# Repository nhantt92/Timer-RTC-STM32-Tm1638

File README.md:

# Timer-control-boar-hw

- Timer-control-board-hw

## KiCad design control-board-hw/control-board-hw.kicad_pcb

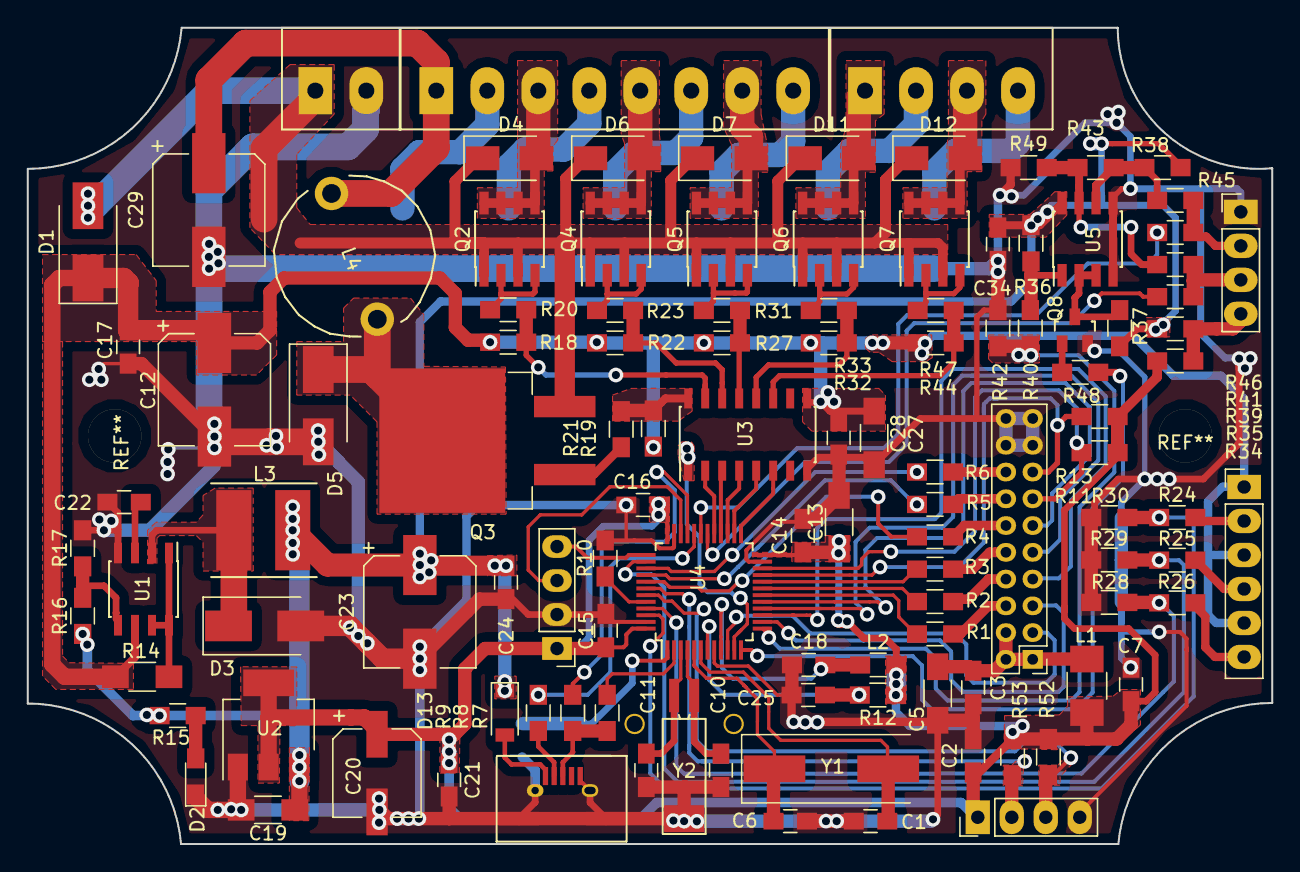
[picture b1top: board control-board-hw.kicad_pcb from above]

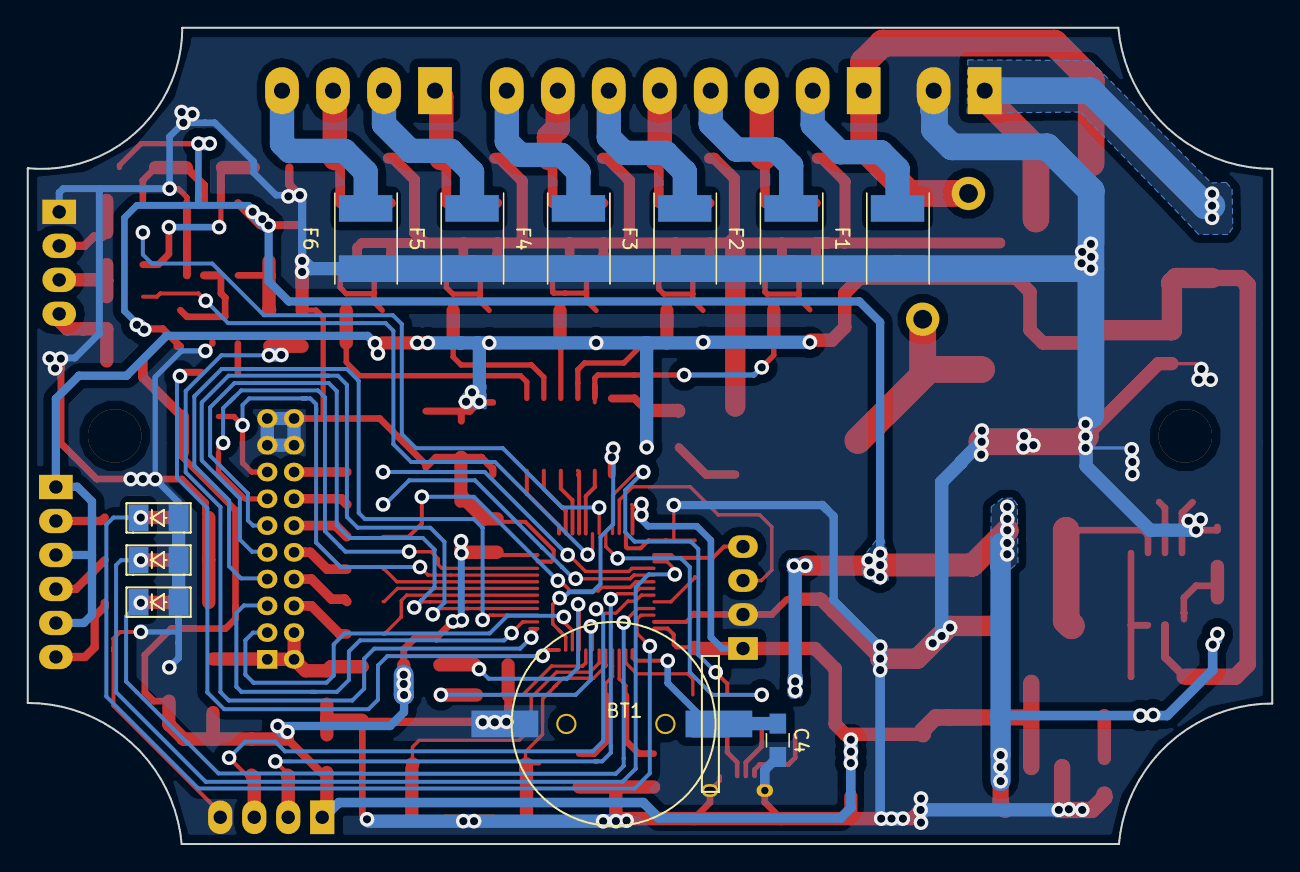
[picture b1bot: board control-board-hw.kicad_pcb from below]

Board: 2 copper layers, 93.0 x 61.0 mm, 125 parts (11 on the bottom side), 97 nets.

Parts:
BT1: Battery_Cell; BT3V3
C1, C6, C10, C11: 22pF; C_0805_HandSoldering
C2, C3, C4, C7, C14, C15, C16, C17, C18, C21, C24, C25, C28, C34: 100nF; C_0805_HandSoldering
C5, C13, C19, C27: 10uF; C_1206_HandSoldering
C12, C23, C29: CP1; CP_Elec_8x10.5
C20: CP1; CP_Elec_6.3x7.7
C22: 33p; C_0805_HandSoldering
D1: D_ALT; D_SMB_Handsoldering
D2: LED; LED_0805_HandSoldering
D3, D5: D_Schottky; D_SMB_Handsoldering
D4, D6, D7, D11, D12: D_Schottky; D_SMA_Standard
D8, D9, D10: 3V3; SOD-80
D13: D_ALT; D_SOD-123
F1, F2, F3, F4, F5, F6: 10A/24V; Fuse_SMD1812
J1: CONN_02X10; Pin_Header_Straight_2x10_Pitch2.00mm
J3: CONN_01X04; Pin_Header_Straight_1x04_Pitch2.54mm
J5: CONN_01X08; TerminalBlock_Pheonix_PT-3.81mm_8pol
J6: CONN_01X06; Header-6pin-2.54
J7: USB_OTG; USB_Micro-B
J8, J9: CONN_01X04; Header-4pin-2.54
J10: CONN_01X02; TerminalBlock_Pheonix_PT-3.81mm_2pol
J11: CONN_01X04; TerminalBlock_Pheonix_PT-3.81mm_4pol
L1: L_Small; R_1210_HandSoldering
L2: L_Small; R_0805_HandSoldering
L3: L_Small; Inductor_5.2x5.8x4.5
L4: L; Neosid_Inductor_Sd12k-style1
Q2, Q4, Q5, Q6, Q7: AMP4953; SOIC-8_3.9x4.9mm_Pitch1.27mm
Q3: Q_PMOS_GDS; TO-263-2Lead
Q8: C1815; SOT-23
R1, R2, R3, R4, R5, R6, R34, R35, R39, R41, R45, R46: 0R; R_0805_HandSoldering
R7: 1.5k; R_0805_HandSoldering
R8, R9: 22R; R_0805_HandSoldering
R10, R12, R18, R19, R22, R27, R28, R29, R30, R32, R36, R37, R42, R44: 10k; R_0805_HandSoldering
R11, R13, R40, R52, R53: 4.7k; R_0805_HandSoldering
R14: 0.15; R_1206_HandSoldering
R15: 1k; R_0805_HandSoldering
R16: 3K/1%; R_0805_HandSoldering
R17: 1k/1%; R_0805_HandSoldering
R20, R21, R23, R31, R33, R47: 10R; R_0805_HandSoldering
R24, R25, R26: 27k; R_0805_HandSoldering
R38, R49: 20k; R_0805_HandSoldering
R43: 120; R_0805_HandSoldering
R48: 2.2k; R_0805_HandSoldering
U1: MC34063; SOIC-8_3.9x4.9mm_Pitch1.27mm
U2: ASM1117; SOT-223
U3: ULN2003; SOIC-16_3.9x9.9mm_Pitch1.27mm
U4: STM32F103C8; LQFP-48_7x7mm_Pitch0.5mm
U5: MAX485; SOIC-8_3.9x4.9mm_Pitch1.27mm
Y1: Crystal; Crystal_SMD_HC49-SD
Y2: Crystal_GND3; Crystal_Round_Horizontal_3mm_smd

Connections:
+3V3: C2.1, C7.2, C13.1, C14.1, C15.1, C16.1, C20.1, C21.1, J3.1, J9.1, L1.2, L2.1, R11.1, R12.1, R13.1, R34.1, R52.1, R53.1, U2.2, U2.4, U4.24, U4.36, U4.48
+5V: C19.1, C23.1, C24.1, C34.2, D13.1, L3.2, R15.2, R16.1, R35.1, R36.1, R37.1, R38.1, U2.3, U5.8
+12V: C12.1, C17.1, C27.2, C28.2, D1.1, J6.1, J6.3, J6.5, R14.1, R18.1, R19.1, R22.1, R27.1, R32.1, R44.1, U1.6, U3.9
/control-monitor/A: R38.2, R43.1, R45.1, U5.6
/control-monitor/B: R41.1, R43.2, R49.1, U5.7
/control-monitor/RX: R46.1, U4.31
/control-monitor/RX_485: R40.1, R42.1, U4.13
/control-monitor/SCL2: J9.2, R53.2, U4.42
/control-monitor/SDA2: J9.3, R52.2, U4.43
/control-monitor/SPRAY: C29.1, J5.1, L4.2
/control-monitor/TX: R39.1, U4.30
/control-monitor/TX_485: R48.1, U4.12
/control-monitor/WATER_H: D10.1, R24.1, R30.1, U4.46
/control-monitor/WATER_L: D8.1, R26.1, R28.1, U4.45
/control-monitor/WATER_M: D9.1, R25.1, R29.1, U4.38
/control-monitor/ctrl1: R18.2, R20.2, U3.15
/control-monitor/ctrl2: R22.2, R23.2, U3.14
/control-monitor/ctrl3: R27.2, R31.2, U3.13
/control-monitor/ctrl4: R32.2, R33.2, U3.12
/control-monitor/ctrl5: R44.2, R47.2, U3.11
/control-monitor/ctrl_SPRAY: R19.2, R21.2, U3.16
/control-monitor/ext_out1: U3.5, U4.26
/control-monitor/ext_out2: U3.6, U4.25
/control-monitor/out1: D4.2, J5.3, Q2.5, Q2.6, Q2.7, Q2.8
/control-monitor/out2: D6.2, J5.5, Q4.5, Q4.6, Q4.7, Q4.8
/control-monitor/out3: D7.2, J5.7, Q5.5, Q5.6, Q5.7, Q5.8
/control-monitor/out4: D11.2, J11.1, Q6.5, Q6.6, Q6.7, Q6.8
/control-monitor/out5: D12.2, J11.3, Q7.5, Q7.6, Q7.7, Q7.8
/control-monitor/oxi: U3.4, U4.27
/control-monitor/pump1: U3.2, U4.29
/control-monitor/spray_ctrl: U3.1, U4.11
/control-monitor/valve: U3.3, U4.28
/mcu/CS: J1.5, U4.14
/mcu/LCD_SCL: J1.15, R13.2, U4.21
/mcu/LCD_SDA: J1.13, R11.2, U4.22
/mcu/MISO: J1.9, U4.16
/mcu/MOSI: J1.11, U4.17
/mcu/OSC32I: C11.2, U4.3, Y2.2
/mcu/OSC32O: C10.2, U4.4, Y2.1
/mcu/OSCI: C6.1, U4.5, Y1.1
/mcu/OSCO: C1.1, U4.6, Y1.2
/mcu/RST: J1.3, U4.10
/mcu/SCK: J1.7, U4.15
/mcu/SWCLK: J3.4, U4.37
/mcu/SWDIO: J3.3, U4.34
/mcu/key1: R1.1, U4.18
/mcu/key2: R2.1, U4.19
/mcu/key3: R3.1, U4.20
/mcu/key4: R4.1, U4.41
/mcu/key5: R5.1, U4.40
/mcu/key6: R6.1, U4.39
/mcu/usb_dis: R7.2, U4.2
/mcu/usb_dm: R9.2, U4.32
/mcu/usb_dp: R8.2, U4.33
GND: BT1.2, C1.2, C2.2, C3.1, C4.2, C5.1, C6.2, C7.1, C10.1, C11.1, C12.2, C13.2, C14.2, C15.2, C16.2, C17.2, C18.1, C19.2, C20.2, C21.2, C22.2, C23.2, C24.2, C25.2, C27.1, C28.1, C29.2, C34.1, D2.1, D3.2, D5.2, D8.2, D9.2, D10.2, F1.1, F2.1, F3.1, F4.1, F5.1, F6.1, J1.17, J1.18, J1.19, J1.20, J3.2, J7.5, J7.6, J8.1, J9.4, J10.2, Q8.2, R10.2, R17.2, R28.2, R29.2, R30.2, R42.2, R49.2, U1.4, U2.1, U3.8, U4.8, U4.23, U4.35, U4.47, U5.4, U5.5, Y2.3
unnamed: BT1.1, C4.1, U4.1
unnamed: C3.2, C5.2, J1.1, J1.2, J1.4, L1.1
unnamed: C18.2, L2.2, U4.9
unnamed: C22.1, U1.3
unnamed: C25.1, R12.2, U4.7
unnamed: D2.2, R15.1
unnamed: D3.1, L3.1, U1.2
unnamed: D5.1, L4.1, Q3.2
unnamed: D13.2, J7.1
unnamed: F1.2, J5.2
unnamed: F2.2, J5.4
unnamed: F3.2, J5.6
unnamed: F4.2, J5.8
unnamed: F5.2, J11.2
unnamed: F6.2, J11.4
unnamed: J1.6, R1.2
unnamed: J1.8, R2.2
unnamed: J1.10, R3.2
unnamed: J1.12, R4.2
unnamed: J1.14, R5.2
unnamed: J1.16, R6.2
unnamed: J6.2, R24.2
unnamed: J6.4, R25.2
unnamed: J6.6, R26.2
unnamed: J7.2, R9.1
unnamed: J7.3, R7.1, R8.1
unnamed: J8.2, R45.2, R46.2
unnamed: J8.3, R39.2, R41.2
unnamed: J8.4, R34.2, R35.2
unnamed: Q2.2, Q2.4, R20.1
unnamed: Q3.1, R21.1
unnamed: Q4.2, Q4.4, R23.1
unnamed: Q5.2, Q5.4, R31.1
unnamed: Q6.2, Q6.4, R33.1
unnamed: Q7.2, Q7.4, R47.1
unnamed: Q8.1, R48.2
unnamed: Q8.3, R37.2, U5.2, U5.3
unnamed: R10.1, U4.44
unnamed: R14.2, U1.1, U1.7, U1.8
unnamed: R16.2, R17.1, U1.5
unnamed: R36.2, R40.2, U5.1
VCC: D1.2, D4.1, D6.1, D7.1, D11.1, D12.1, J10.1, Q2.1, Q2.3, Q3.3, Q4.1, Q4.3, Q5.1, Q5.3, Q6.1, Q6.3, Q7.1, Q7.3

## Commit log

2018-01-16 upload project
2018-01-16 init fw
2018-01-17 fix structure project
